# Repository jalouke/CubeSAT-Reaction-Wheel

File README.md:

# CubeSAT-Reaction-Wheel

Portland State University is developing Oregon’s first orbital satellite, a 2U Cubesat dubbed Oresat. This cubesat will use a reaction wheel system for attitude control and pointing of the onboard antennas and cameras. I am developing the controller, designing the structure and sourcing hardware for both the space rated system and a ground test system that will also be used for demonstration purposes. This system has been tested using the Dryden Drop Tower at PSU as well as in captive hanging tests. The current controller is a simple proportional controller, however using data collected from the drop test I will refine the model and implement a more sophisticated controller. Video of the tests can be seen at:  [Captive Controller Hanging Test](https://www.youtube.com/watch?v=Is1gPHlewtgand) and [Dryden Drop Tower Micro-Gravity Test](https://www.youtube.com/watch?v=cC2FpmCP5B4)

Both of the previous tests were conducted using a simple open loop proportional controller that was tuned via test to induce a slightly underdamped response. This was to create data that can be more easily compared to an ideal model.

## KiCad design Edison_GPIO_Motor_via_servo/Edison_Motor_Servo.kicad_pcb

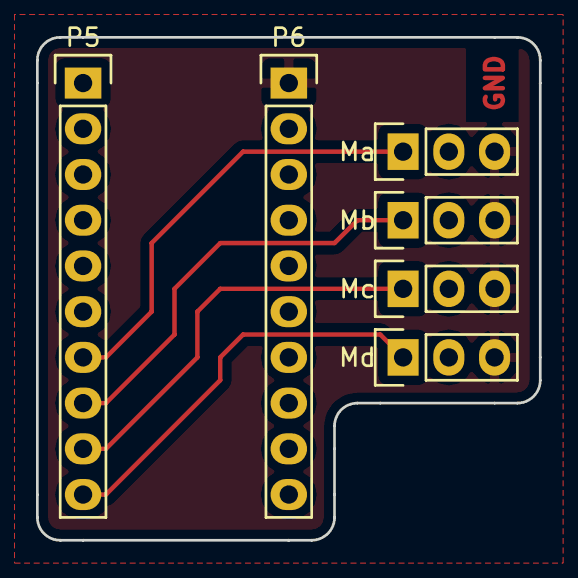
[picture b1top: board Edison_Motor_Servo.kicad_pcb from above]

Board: 2 copper layers, 27.9 x 27.9 mm, 6 parts (0 on the bottom side), 5 nets.

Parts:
Ma: CONN_01X03; Socket_Strip_Straight_1x03
Mb: CONN_01X03; Socket_Strip_Straight_1x03
Mc: CONN_01X03; Socket_Strip_Straight_1x03
Md: CONN_01X03; Socket_Strip_Straight_1x03
P5, P6: CONN_01X10; Socket_Strip_Straight_1x10

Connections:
GND: Ma.3, Mb.3, Mc.3, Md.3, P6.1
unnamed: Ma.1, P5.7
unnamed: Mb.1, P5.8
unnamed: Mc.1, P5.9
unnamed: Md.1, P5.10

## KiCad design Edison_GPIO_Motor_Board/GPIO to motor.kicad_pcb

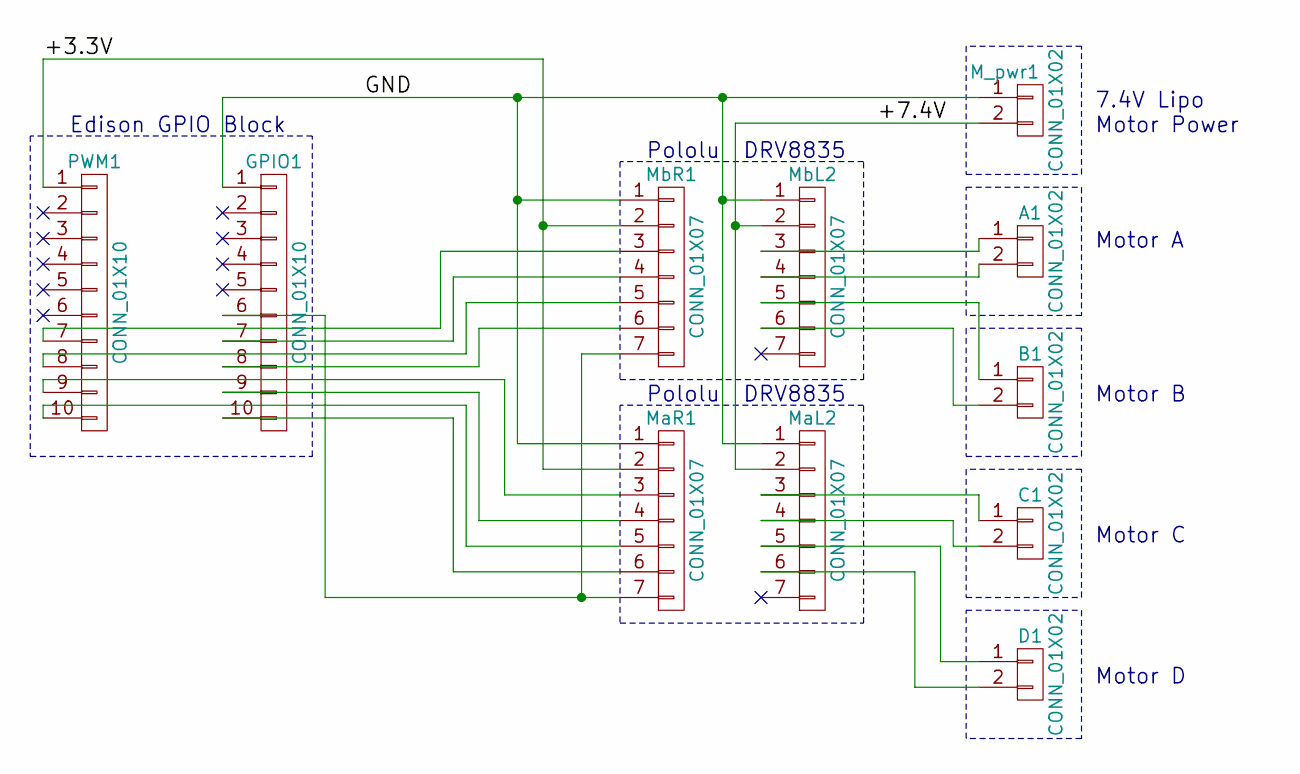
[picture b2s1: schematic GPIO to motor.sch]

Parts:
A1: CONN_01X02; Pin_Header_Straight_1x02
B1: CONN_01X02; Pin_Header_Straight_1x02
C1: CONN_01X02; Pin_Header_Straight_1x02
D1: CONN_01X02; Pin_Header_Straight_1x02
GPIO1: CONN_01X10; Pin_Header_Straight_1x10
M_pwr1: CONN_01X02; Pin_Header_Straight_1x02
MaL2: CONN_01X07; Pin_Header_Straight_1x07
MaR1: CONN_01X07; Pin_Header_Straight_1x07
MbL2: CONN_01X07; Pin_Header_Straight_1x07
MbR1: CONN_01X07; Pin_Header_Straight_1x07
PWM1: CONN_01X10; Pin_Header_Straight_1x10

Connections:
+3V3: MaR1.2, MbR1.2, PWM1.1
+BATT: M_pwr1.2, MaL2.2, MbL2.2
GND: GPIO1.1, M_pwr1.1, MaL2.1, MaR1.1, MbL2.1, MbR1.1
unnamed: A1.1, MbL2.3
unnamed: A1.2, MbL2.4
unnamed: B1.1, MbL2.5
unnamed: B1.2, MbL2.6
unnamed: C1.1, MaL2.3
unnamed: C1.2, MaL2.4
unnamed: D1.1, MaL2.5
unnamed: D1.2, MaL2.6
unnamed: GPIO1.6, MaR1.7, MbR1.7
unnamed: GPIO1.7, MbR1.4
unnamed: GPIO1.8, MbR1.6
unnamed: GPIO1.9, MaR1.4
unnamed: GPIO1.10, MaR1.6
unnamed: MaR1.3, PWM1.9
unnamed: MaR1.5, PWM1.10
unnamed: MbR1.3, PWM1.7
unnamed: MbR1.5, PWM1.8

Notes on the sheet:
Edison GPIO Block
Pololu DRV8835
Motor A
Motor B
Motor C
Motor D
7.4V Lipo Motor Power

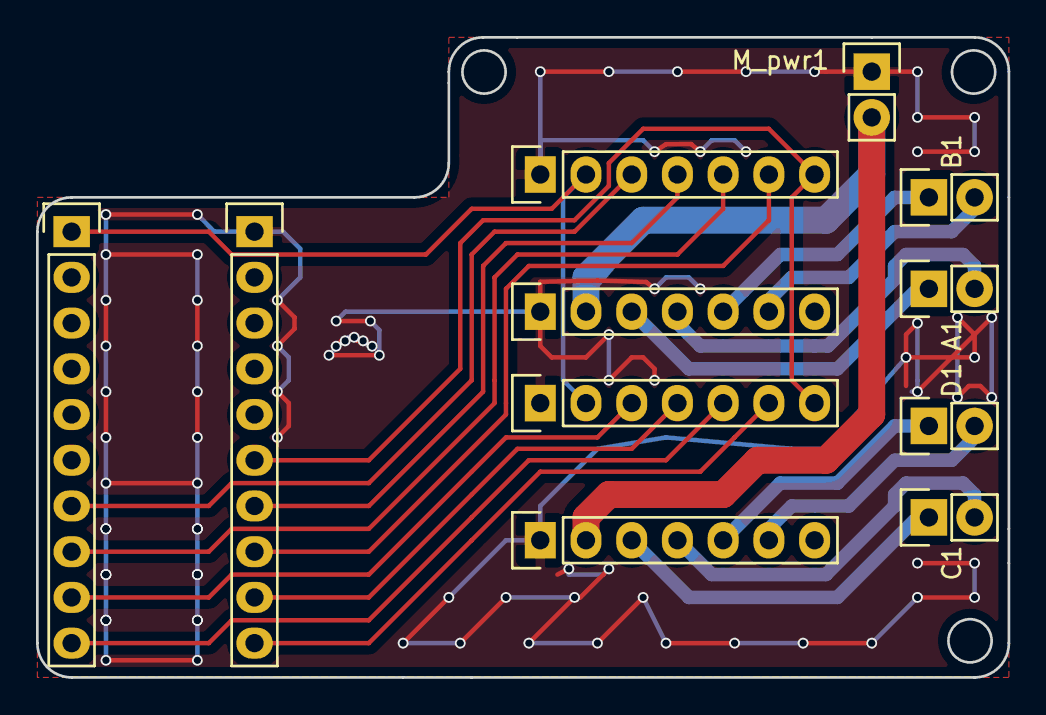
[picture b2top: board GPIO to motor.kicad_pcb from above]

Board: 2 copper layers, 54.0 x 35.6 mm, 11 parts (0 on the bottom side), 20 nets.

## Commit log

2016-01-22 :confetti_ball: Added .gitattributes & .gitignore files
2016-01-22 Adding work up to this point
    Includes Solidworks CAD models, Datasheets, and Board for GPIO to motor
    drivers
2016-02-02 adding code
    CubeSAT_RCS.py is the main controller for the cubsat
    gpio_off.py is to sutdown all I/O pins
    GYR_cal.py is to determine gyro offsets
    IMU.py is the program that reads data from the IMU (this is called by
    CubeSAT_RCS.py only)
    LSM9DS0.py is a list of registers that are used by the IMU
2016-02-02 updating description
2016-02-23 Updated CAD to V2
    includes brushless motors, ESC, lipo batteries, and controller boards
2016-02-23 modified the reaction wheel to add extra clearance
    and did a simple FEA of the wheel rotating at 22,000 RPM
2016-02-23 adding circuit board for GPIO to motor speed controller, and cubesat model made with octave
2016-02-25 working on the controller simulation
2016-02-26 added AIAA Space conference proceedings abstract draft
2016-02-27 updating the simulation
2016-02-27 replotted gerbers for servo board
2016-02-27 I forgot to measure the header spacing :(
2016-02-27 try again
2016-03-14 updated open-loop system model, added screenshot of motor response graph
2016-03-31 refining model
2016-04-26 Updated dynamics model of the cubesat reaction wheel system. Model includes a PIcontroller that is untuned
2016-04-29 Adding Drop test data, updating cube code to latest versions and adding drop test code
2016-05-04 Analysis of Drop test on 4-26 and comparison to model
2016-05-04 update readme with nifty video and picture
2016-05-11 updated model script, created output graphs from the model
2016-05-19 started cubesat model notebook for jeremy
2016-05-19 automated path of script in code
2016-05-19 modified cubesat model code to just go through the first few parts in an ipython notebook and commented out the rest but its still all there
2016-05-25 renamed files that hate windows
2016-05-25 adding bode analysis drop test code
2016-06-01 Figured out how return just the value
2016-06-07 Adding drop test code changes
2016-06-08 fixed drop test code for bode analysis.
2016-06-08 Merge
2016-10-16 forgot to upload previous changes
